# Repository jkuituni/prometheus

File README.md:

# Prometheus

Prometheus is a WDC 65816 based SingleBoardComputer aimed to be a fully usable self-containing computer platform.

System specification:

* CPU: WDC 65816 at 8MHz
* ROM: 8kB Firmware boot EPROM
* RAM: Up to 16MB of RAM via 4x 30pin SIMMs
* Video: Custom graphics chip "GRACE"
* Audio: Ensoniq EN5503 DOC
* I/O: 
  - RS232 serial port
  - Centronics port
  - 2x Atari "standard" joystick ports
  - ps/2 keyboard port
  - IDE massstorage interface
  - Standard floppydrive interface
* Other: 
  - DS1501 Realtime clock
  - 2x 16bit expansion slot connectors
  - 8bit expansion header

The graphics is implemented with a custom video controller called "[GRaCE](https://github.com/jkuituni/GRaCE)" using an additional FPGA board that connects via the two 40pin connectors. 

System controller is a CPLD that ties in the system, It generates the chip selects, various control signals and contains a DRAM controller.

More accurate specifications regarding the memory layout, graphics capabilities and generic system description will be 
added as they become available.

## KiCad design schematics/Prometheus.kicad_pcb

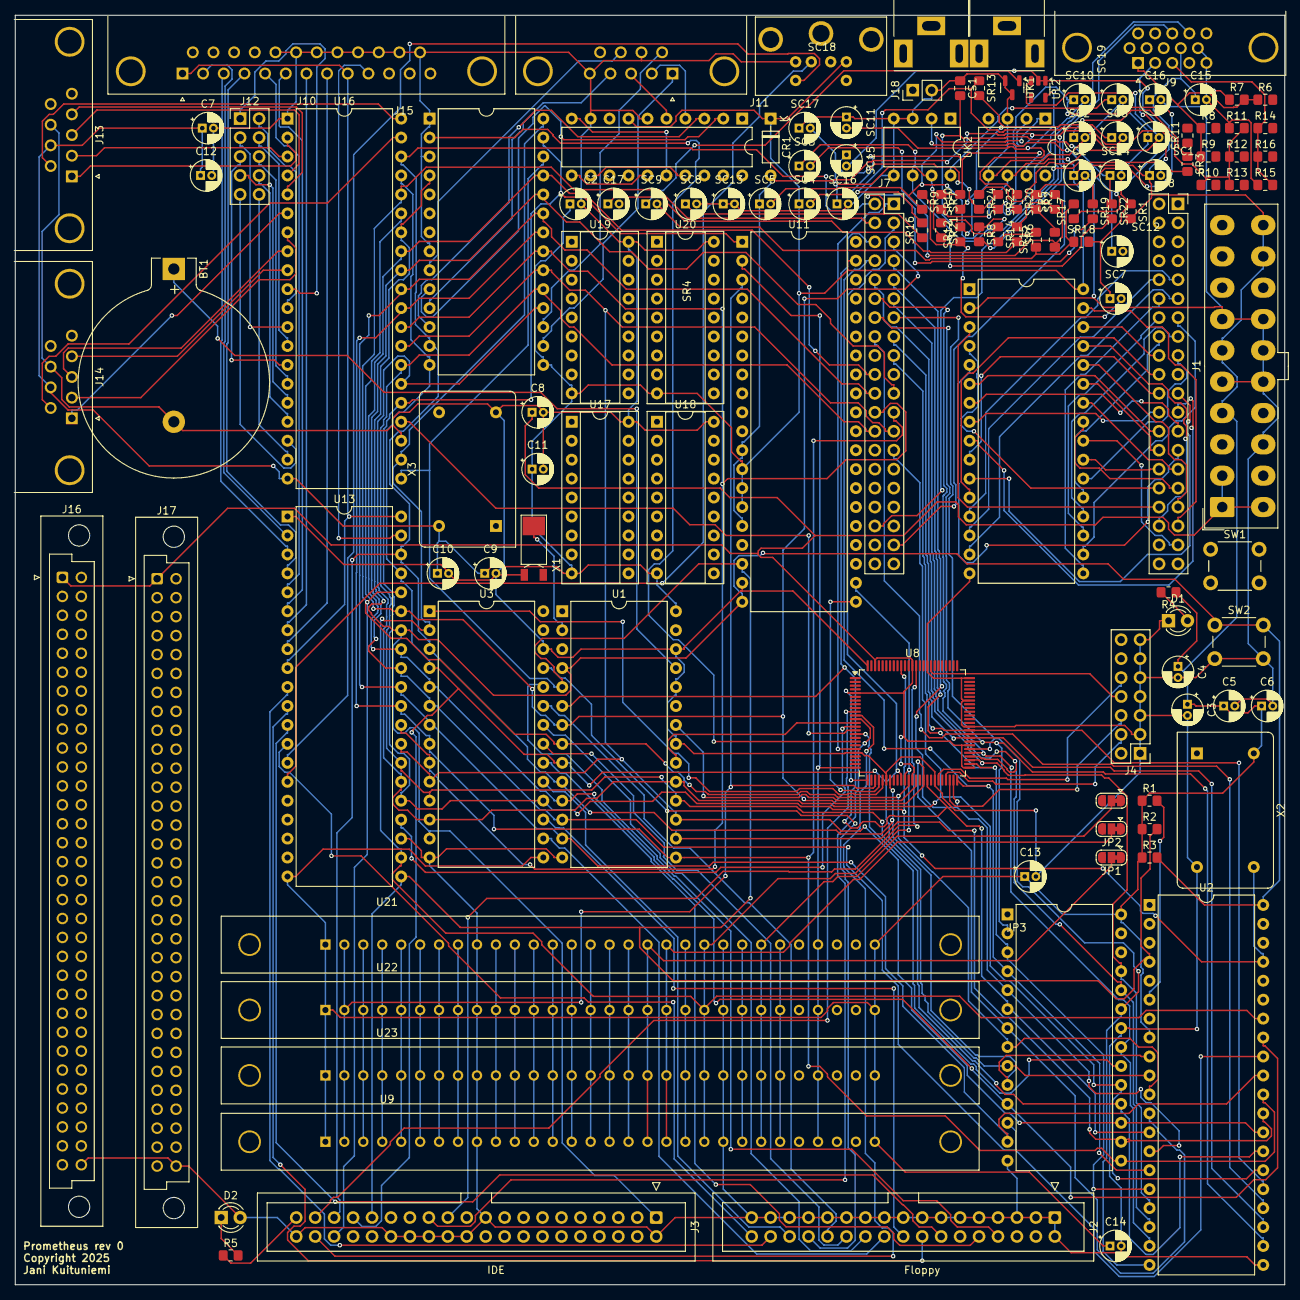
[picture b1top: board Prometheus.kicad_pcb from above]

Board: 2 copper layers, 170.2 x 170.2 mm, 130 parts (0 on the bottom side), 191 nets.

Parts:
BT1: Battery; BatteryHolder_Keystone_104_1x23mm
C1, C2, C3, C4, C5, C6, C7, C8, C9, C10, C11: 0.1uF; CP_Radial_D4.0mm_P1.50mm
C12, C13, C14, C15, C16: C; CP_Radial_D4.0mm_P1.50mm
C17: 0.1u; CP_Radial_D4.0mm_P1.50mm
CR1: 1N914; D_DO-35_SOD27_P7.62mm_Horizontal
CS1: .1u; R_0805_2012Metric_Pad1.20x1.40mm_HandSolder
D1: Power LED; LED_D3.0mm
D2: IDE LED; LED_D3.0mm
J1: ATX Power Conn; Molex_Mini-Fit_Jr_5566-20A_2x10_P4.20mm_Vertical
J2: FDC Connector; IDC-Header_2x17_P2.54mm_Vertical
J3: IDE Connector; IDC-Header_2x20_P2.54mm_Vertical
J4: JTAG; PinHeader_2x07_P2.54mm_Vertical
J5: Left Audio; RCA
J6: Right Audio; RCA
J7: GRACE board interface 1; PinSocket_2x20_P2.54mm_Vertical
J8: GRACE board interface 2; PinSocket_2x20_P2.54mm_Vertical
J9: 15kHz Video Out; DSUB-15-HD_Female_Horizontal_P2.29x1.98mm_EdgePinOffset3.03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
J10: Centronics; DSUB-25_Female_Horizontal_P2.77x2.84mm_EdgePinOffset4.94mm_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
J11: ps/2 keyb; MINI-DIN-6-FULL-SHIELD
J12: Expansion; PinHeader_2x05_P2.54mm_Vertical
J13: Joy1; DSUB-9_Female_Horizontal_P2.77x2.84mm_EdgePinOffset4.94mm_H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
J14: Joy2; DSUB-9_Female_Horizontal_P2.77x2.84mm_EdgePinOffset4.94mm_H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
J15: rs232; DSUB-9_Male_Horizontal_P2.77x2.84mm_EdgePinOffset4.94mm_Hou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
J16, J17: DIN41612_02x32_AB; DIN41612_B_2x32_Female_Vertical_THT
J18: SPEAKER; PinHeader_1x02_P2.54mm_Vertical
JP1, JP2, JP3: Jumper_2_Open; SolderJumper-3_P1.3mm_Bridged12_RoundedPad1.0x1.5mm
R1, R2, R3, R5: R330; R_0805_2012Metric_Pad1.20x1.40mm_HandSolder
R4, R14: R470; R_0805_2012Metric_Pad1.20x1.40mm_HandSolder
R6, R10: R1100; R_0805_2012Metric_Pad1.20x1.40mm_HandSolder
R7, R11, R15: R150; R_0805_2012Metric_Pad1.20x1.40mm_HandSolder
R8, R12: R560; R_0805_2012Metric_Pad1.20x1.40mm_HandSolder
R9, R13: R270; R_0805_2012Metric_Pad1.20x1.40mm_HandSolder
R16: R240; R_0805_2012Metric_Pad1.20x1.40mm_HandSolder
SC1, SC4, SC5, SC6, SC7: 10p; CP_Radial_D4.0mm_P1.50mm
SC2, SC12, SC17: .1u; CP_Radial_D4.0mm_P1.50mm
SC3, SC9, SC16, SC19: 22u; CP_Radial_D4.0mm_P1.50mm
SC8: 1.5n; CP_Radial_D4.0mm_P1.50mm
SC10, SC15: 3.9n; CP_Radial_D4.0mm_P1.50mm
SC11: 220p; CP_Radial_D4.0mm_P1.50mm
SC13: 1.8n; CP_Radial_D4.0mm_P1.50mm
SC14: 470u/16v; CP_Radial_D4.0mm_P1.50mm
SC18: 560p; CP_Radial_D4.0mm_P1.50mm
SR1, SR4: 1K; R_0805_2012Metric_Pad1.20x1.40mm_HandSolder
SR2: 560; R_0805_2012Metric_Pad1.20x1.40mm_HandSolder
SR3: 2.7; R_0805_2012Metric_Pad1.20x1.40mm_HandSolder
SR5: 220; R_0805_2012Metric_Pad1.20x1.40mm_HandSolder
SR6: 100; R_0805_2012Metric_Pad1.20x1.40mm_HandSolder
SR7, SR8, SR9, SR10, SR12, SR13: 3.9K; R_0805_2012Metric_Pad1.20x1.40mm_HandSolder
SR11: 200K; R_0805_2012Metric_Pad1.20x1.40mm_HandSolder
SR14, SR15: 470K; R_0805_2012Metric_Pad1.20x1.40mm_HandSolder
SR16, SR19, SR20: 15K; R_0805_2012Metric_Pad1.20x1.40mm_HandSolder
SR17, SR18, SR23, SR24: 10K; R_0805_2012Metric_Pad1.20x1.40mm_HandSolder
SR21, SR22: 200; R_0805_2012Metric_Pad1.20x1.40mm_HandSolder
SW1: Power Switch; SW_PUSH_6mm
SW2: Reset Switch; SW_PUSH_6mm
U1: DS1501YN; DIP-28_W15.24mm
U2: wdc65c816; DIP-40_W15.24mm
U3: WD1772; DIP-28_W15.24mm
U8: XC9572XL-TQ100; TQFP-100_14x14mm_P0.5mm
U9, U21, U22, U23: SIMM16M; SIMM
U10: 2764; DIP-28_W15.24mm
U11: EN5503DOC; DIP-40_W15.24mm
U12: VRAM; DIP-32_W15.24mm
U13, U16: wdc65c22; DIP-40_W15.24mm
U14: wdc65c51; DIP-28_W15.24mm
U15: MAX233CPP; DIP-20_W7.62mm
U17, U18, U19, U20: 41464; DIP-18_W7.62mm_Socket
UK1: LM3340; SOT-23
UK2: LM380N-8; DIP-8_W7.62mm
UL1: MC34084; DIP-8_W7.62mm
UL2: TL072; SOT-23-5
X1: 32kHz; Crystal_SMD_FrontierElectronics_FM206
X2: 8MHz; Oscillator_DIP-14
X3: 1.8432MHz; Oscillator_DIP-14

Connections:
+12V: SC16.1, SC17.2, SR21.2, SR22.2, UK2.7 (VS)
/Audio/SND-SIG-: CR1.2 (A), SC1.2, SC5.1, SR8.2, U11.12 (VOLFDBK), U11.16 (SIG-), UL1.2 (-)
/Audio/SOUND.H: SR2.2, SR4.2
/RAM & ROM/DQ0: U9.3 (DQ0), U21.3 (DQ0), U22.3 (DQ0), U23.3 (DQ0)
/RAM & ROM/DQ1: U9.6 (DQ1), U21.6 (DQ1), U22.6 (DQ1), U23.6 (DQ1)
/RAM & ROM/DQ2: U9.10 (DQ2), U21.10 (DQ2), U22.10 (DQ2), U23.10 (DQ2)
/RAM & ROM/DQ3: U9.13 (DQ3), U21.13 (DQ3), U22.13 (DQ3), U23.13 (DQ3)
/RAM & ROM/DQ4: U9.16 (DQ4), U21.16 (DQ4), U22.16 (DQ4), U23.16 (DQ4)
/RAM & ROM/DQ5: U9.20 (DQ5), U21.20 (DQ5), U22.20 (DQ5), U23.20 (DQ5)
/RAM & ROM/DQ6: U9.23 (DQ6), U21.23 (DQ6), U22.23 (DQ6), U23.23 (DQ6)
/RAM & ROM/DQ7: U9.25 (DQ7), U21.25 (DQ7), U22.25 (DQ7), U23.25 (DQ7)
A0: J3.35, J7.2, U1.10 (A0), U2.9 (A0), U3.3 (A0), U8.32, U10.10 (A0), U13.38 (RS0), U14.13 (RS0), U16.38 (RS0)
A1: J3.33, J7.3, U1.9 (A1), U2.10 (A1), U3.4 (A1), U8.35, U10.9 (A1), U13.37 (RS1), U14.14 (RS1), U16.37 (RS1)
A2: J3.36, J7.4, U1.8 (A2), U2.11 (A2), U8.37, U10.8 (A2), U13.36 (RS2), U16.36 (RS2)
A3: J7.5, U1.7 (A3), U2.12 (A3), U8.41, U10.7 (A3), U13.35 (RS3), U16.35 (RS3)
A4: J7.6, U1.6 (A4), U2.13 (A4), U8.42, U10.6 (A4)
A5: J7.7, U2.14 (A5), U8.49, U10.5 (A5)
A6: J7.8, U2.15 (A6), U8.50, U10.4 (A6)
A7: J7.9, U2.16 (A7), U8.52, U10.3 (A7)
A8: J7.10, U2.17 (A8), U8.53, U10.25 (A8)
A9: J7.11, U2.18 (A9), U8.54, U10.24 (A9)
A10: J7.12, U2.19 (A10), U8.55, U10.21 (A10)
A11: J7.13, U2.20 (A11), U8.56, U10.23 (A11)
A12: J7.14, U2.22 (A12), U8.58, U10.2 (A12)
A13: J7.15, U2.23 (A13), U8.59
A14: J7.16, U2.24 (A14), U8.60
A15: J7.17, U2.25 (A15), U8.61
AUDIO_EN: U8.29, U11.21 (~CS)
CAS: U8.28, U9.2 (CAS), U11.3 (~CAS), U21.2 (CAS), U22.2 (CAS), U23.2 (CAS)
D0: J7.20, U1.11 (DQ0), U2.33 (D0), U3.5 (DAL0), U10.11 (D0), U13.33 (D0), U14.25 (D7), U16.33 (D0)
D1: J7.21, U1.12 (DQ1), U2.32 (D1), U3.6 (DAL1), U10.12 (D1), U13.32 (D1), U14.24 (D6), U16.32 (D1)
D2: J7.22, U1.13 (DQ2), U2.31 (D2), U3.7 (DAL2), U10.13 (D2), U13.31 (D2), U14.23 (D5), U16.31 (D2)
D3: J7.23, U1.15 (DQ3), U2.30 (D3), U3.8 (DAL3), U10.15 (D3), U13.30 (D3), U14.22 (D4), U16.30 (D3)
D4: J7.24, U1.16 (DQ4), U2.29 (D4), U3.9 (DAL4), U10.16 (D4), U13.29 (D4), U14.21 (D3), U16.29 (D4)
D5: J7.25, U1.17 (DQ5), U2.28 (D5), U3.10 (DAL7), U10.17 (D5), U13.28 (D5), U14.20 (D2), U16.28 (D5)
D6: J7.26, U1.18 (DQ6), U2.27 (D6), U3.11 (DAL6), U10.18 (D6), U13.27 (D6), U14.19 (D1), U16.27 (D6)
D7: J7.27, U1.19 (DQ7), U2.26 (D7), U3.12 (DAL7), U10.19 (D7), U13.26 (D7), U14.18 (D0), U16.26 (D7)
FDC_DRVA: J2.14, U13.12 (PB2)
FDC_DSKCHG: J2.34, U13.13 (PB3)
FDC_EN: U3.1 (~CS), U8.30
FDC_MTREN: J2.16, U13.11 (PB1)
FDC_SIDE: J2.32, U13.10 (PB0)
GND: BT1.2 (-), C1.2, C2.2, C3.2, C4.2, C5.2, C6.2, C7.2, C8.2, C9.2, C10.2, C11.2, C12.2, C13.2, C14.2, C15.2, C16.2, D1.1 (K), D2.2 (A), J1.5, J1.7, J1.13, J1.15, J1.16, J1.17, J2.1, J2.2, J2.3, J2.5, J2.7, J2.9, J2.11, J2.13, J2.15, J2.17, J2.19, J2.21, J2.23, J2.25, J2.27, J2.29, J2.31, J2.33, J3.2, J3.19, J3.22, J3.24, J3.26, J3.28, J3.30, J3.40, J4.1, J4.3, J4.5, J4.7, J4.9, J4.11, J4.13, J9.5, J9.10, J10.18, J10.19, J10.20, J10.21, J10.22, J10.23, J10.24, J10.25, J11.3, J13.8, J14.8, J15.5, J15.7, J16.b32, J17.b32, R7.1, R11.1, R15.1, SR2.1, SW2.2 (B), U1.14 (GND), U1.21 (GND), U1.24 (~KS), U1.26 (Vbaux), U2.21 (VSS), U3.14 (GND), U3.26 (~DDEN), U8.21 (GND), U8.31 (GND), U8.44 (GND), U8.62 (GND), U8.69 (GND), U8.75 (GND), U8.84 (GND), U8.100 (GND), U9.9 (GND), U9.22 (GND), U10.14 (GND), U10.22 (~OE), U11.19 (VSS), U12.2 (A16), U12.16 (GND), U13.1 (Vss), U13.23 (~CS2), U14.1 (VSS), U14.3 (~CS1), U14.8 (~RTS), U15.6 (GND), U15.9 (GND), U16.1 (Vss), U16.23 (~CS2), U17.18 (GND), U18.18 (GND), U19.18 (GND), U20.18 (GND), U21.9 (GND), U21.22 (GND), U22.9 (GND), U22.22 (GND), U23.9 (GND), U23.22 (GND), X1.2 (GND), X2.7 (GND), X3.7 (GND)
GNDA: CS1.1, J18.2, SC2.2, SC7.1, SC8.2, SC11.1, SC13.1, SC13.2, SC14.2, SC16.2, SC17.1, SC18.1, SC19.2, SR1.1, SR12.2, SR18.2, UK1.2, UK1.3, UK2.3 (-), UK2.4 (GND), UK2.5 (GND), UL1.3 (+), UL1.5 (+)
GNDPWR: C17.1, SR6.2
GRACE_EN: J7.1, U8.20
IDE_CS0: J3.37, U8.10
IDE_CS1: J3.38, U8.11
IOR: J3.25, U8.12
IOW: J3.23, U8.87
IRQ: J3.31, R2.2, U1.5 (~IRQ), U2.4 (~IRQ), U11.18 (~IRQ), U13.21 (~IRQ), U14.26 (~IRQ), U16.21 (~IRQ)
MA0: U9.4 (A0), U21.4 (A0), U22.4 (A0), U23.4 (A0)
MA1: U9.5 (A1), U21.5 (A1), U22.5 (A1), U23.5 (A1)
MA2: U9.7 (A2), U21.7 (A2), U22.7 (A2), U23.7 (A2)
MA3: U9.8 (A3), U21.8 (A3), U22.8 (A3), U23.8 (A3)
MA4: U9.11 (A4), U21.11 (A4), U22.11 (A4), U23.11 (A4)
MA5: U9.12 (A5), U21.12 (A5), U22.12 (A5), U23.12 (A5)
MA6: U9.14 (A6), U21.14 (A6), U22.14 (A6), U23.14 (A6)
MA7: U9.15 (A7), U21.15 (A7), U22.15 (A7), U23.15 (A7)
MA8: U9.17 (A8), U21.17 (A8), U22.17 (A8), U23.17 (A8)
MA9: JP1.1 (A), JP1.2 (B), U9.18 (A9), U21.18 (A9), U22.18 (A9), U23.18 (A9)
MA10: JP2.1 (A), JP2.2 (B), U9.19 (A10), U21.19 (A10), U22.19 (A10), U23.19 (A10)
MA11: JP3.1 (A), JP3.2 (B), U9.24 (A11), U21.24 (A11), U22.24 (A11), U23.24 (A11)
NMI: R1.2, U2.6 (~NMI)
unnamed: BT1.1 (+), U1.25 (Vbat)
unnamed: D1.2 (A), R4.2
unnamed: D2.1 (K), R5.2
unnamed: J2.8, U3.24 (~IP)
unnamed: J2.10, U3.20 (MO)
unnamed: J2.18, U3.17 (DIRC)
unnamed: J2.20, U3.16 (STEP)
unnamed: J2.22, U3.22 (WD)
unnamed: J2.24, U3.21 (WG)
unnamed: J2.26, U3.23 (~TR00)
unnamed: J2.28, U3.25 (~WPRT)
unnamed: J2.30, U3.19 (~RD)
unnamed: J3.39, R5.1
unnamed: J4.4, U8.47 (TMS)
unnamed: J4.6, U8.48 (TCK)
unnamed: J4.8, U8.83 (TDO)
unnamed: J4.10, U8.45 (TDI)
unnamed: J7.36, J9.14
unnamed: J7.37, J9.13
unnamed: J8.9, U12.13 (Q0)
unnamed: J8.10, U12.14 (Q1)
unnamed: J8.11, U12.15 (Q2)
unnamed: J8.12, U12.17 (Q3)
unnamed: J8.13, U12.18 (Q4)
unnamed: J8.14, U12.19 (Q5)
unnamed: J8.15, U12.20 (Q6)
unnamed: J8.16, U12.21 (Q7)
unnamed: J8.17, U12.22 (~CS1)
unnamed: J8.18, U12.30 (CS2)
unnamed: J8.20, U12.12 (A0)
unnamed: J8.21, U12.11 (A1)
unnamed: J8.22, U12.10 (A2)
unnamed: J8.23, U12.9 (A3)
unnamed: J8.24, U12.8 (A4)
unnamed: J8.25, U12.7 (A5)
unnamed: J8.26, U12.6 (A6)
unnamed: J8.27, U12.5 (A7)
unnamed: J8.28, U12.27 (A8)
unnamed: J8.29, U12.26 (A9)
unnamed: J8.30, U12.23 (A10)
unnamed: J8.31, U12.25 (A11)
unnamed: J8.32, U12.4 (A12)
unnamed: J8.33, U12.28 (A13)
unnamed: J8.34, U12.3 (A14)
unnamed: J8.35, U12.31 (A15)
unnamed: J8.36, U12.29 (~WE)
unnamed: J8.37, U12.24 (~OE)
unnamed: J9.1, R6.1, R7.2, R8.1, R9.1
unnamed: J9.2, R10.1, R11.2, R12.1, R13.1
unnamed: J9.3, R14.1, R15.2, R16.1
unnamed: J12.1, U16.10 (PB0)
unnamed: J12.2, U16.11 (PB1)
unnamed: J12.3, U16.12 (PB2)
unnamed: J12.4, U16.13 (PB3)
unnamed: J12.5, U16.14 (PB4)
unnamed: J12.6, U16.15 (PB5)
unnamed: J12.7, U16.16 (PB6)
unnamed: J12.8, U16.17 (PB7)
unnamed: J12.9, U16.18 (CB1)
unnamed: J12.10, U16.19 (CB2)
unnamed: SC3.2, SR4.1, SR5.2
unnamed: SR5.1, SR6.1
unnamed: SR14.2, SR15.2
unnamed: SC2.1, SR3.1
unnamed: SC3.1, SR3.2, UK2.6
unnamed: SC4.2, SR7.1, SR10.2, UL1.7
unnamed: SC5.2, SR8.1, SR9.2, UL1.1
unnamed: SC6.2, SR13.1, SR16.2
unnamed: SC8.1, SR16.1, SR19.2
unnamed: SC9.1, UK1.1
unnamed: SC9.2, SR15.1, SR17.2, SR18.1
unnamed: SC10.1, SR19.1, SR20.2
unnamed: SC15.1, SR23.1, SR24.2
unnamed: CS1.2, SC14.1, SR14.1, SR21.1, SR22.1
unnamed: J10.1, J10.9, U13.9 (PA7), U13.40 (CA1)
unnamed: J10.10, U13.39 (CA2)
unnamed: J10.2, U13.2 (PA0)
unnamed: J10.3, U13.3 (PA1)
unnamed: J10.4, U13.4 (PA2)
unnamed: J10.5, U13.5 (PA3)
unnamed: J10.6, U13.6 (PA4)
unnamed: J10.7, U13.7 (PA5)
unnamed: J10.8, U13.8 (PA6)
unnamed: J11.5, U13.14 (PB4)
unnamed: J11.1, U13.15 (PB5)
unnamed: U14.12 (RxD), U15.3 (R1OUT)
unnamed: U14.10 (TxD), U15.2 (T1IN)
unnamed: J15.8, U14.9 (~CTS)
unnamed: J15.1, U14.16 (~DCD)
unnamed: J15.6, U14.17 (~DSR)
unnamed: J15.4, U14.11 (~DTR)
unnamed: U15.11 (C2+(C2-)), U15.15 (C2+)
unnamed: U15.10 (V-(CS-)), U15.16 (C2-)
unnamed: J15.2, U15.4 (R1IN)
unnamed: J15.3, U15.5 (T1OUT)
unnamed: U15.12 (V-(C2+)), U15.17 (V-)
unnamed: J13.6, U16.40 (CA1)
unnamed: J14.6, U16.39 (CA2)
unnamed: J13.1, U16.2 (PA0)
unnamed: J13.2, U16.3 (PA1)
unnamed: J13.3, U16.4 (PA2)
unnamed: J13.4, U16.5 (PA3)
unnamed: J14.1, U16.6 (PA4)
unnamed: J14.2, U16.7 (PA5)
unnamed: J14.3, U16.8 (PA6)
unnamed: J14.4, U16.9 (PA7)
unnamed: SC12.1, UK2.2 (+)
unnamed: SC19.1, UK2.8 (BYPASS)
unnamed: SC7.2, SR9.1, SR12.1
unnamed: SC6.1, SR10.1, SR13.2
unnamed: SC18.2, SR24.1, UL2.3 (+)
unnamed: SC15.2, SR17.1, UL2.1, UL2.2 (-)
unnamed: SC11.2, SR20.1, UL2.5 (+)
unnamed: SC10.2, SR23.2
PHI2: U2.37 (PHI2), U3.18 (CLK), U8.91, U11.1 (CLK), U13.25 (PHI2), U14.27 (PHI2), U16.25 (PHI2), X2.8 (OUT)
RAS: U8.25, U9.27 (RAS), U11.2 (~RAS), U21.27 (RAS), U22.27 (RAS), U23.27 (RAS)
RES: J3.1, R3.2, SW2.1 (A), U1.4 (~RST), U2.40 (~RES), U3.13 (~MR), U11.20 (RES), U13.34 (~RES), U14.4 (~RES), U16.34 (~RES)
ROM_EN: U8.16, U10.20 (~CE)
RTC_CLK: U1.2 (X1), X1.3 (OUT)
RTC_EN: U1.20 (~CE), U8.13
RW: U2.34 (~RW), U3.2 (~RW), U8.36, U9.21 (WR), U11.22 (~WE), U13.22 (~RW), U14.28 (~RW), U16.22 (~RW), U21.21 (WR), U22.21 (WR), U23.21 (WR)
UART_EN: U8.18, U14.2 (CS0)
VIA1_EN: U8.14, U13.24 (CS1)
VIA2_EN: U8.15, U16.24 (CS1)
Vcc: C1.1, C2.1, C3.1, C4.1, C5.1, C6.1, C7.1, C9.1, C10.1, C11.1, C12.1, C13.1, C14.1, C15.1, C16.1, CR1.1 (K), J1.4, J1.6, J1.19, J1.20, J9.9, J11.4, J13.7, J14.7, R1.1, R2.1, R3.1, R4.1, SC1.1, SC4.1, SR1.2, SR7.2, U1.28 (Vcc), U2.8 (VDD), U3.15 (VCC), U9.1 (VCC), U9.30 (VCC), U10.28 (VCC), U11.13 (VOL-), U11.14 (WVREF), U11.15 (SIG+), U11.39 (VDD), U12.32 (VCC), U13.20 (VDD), U14.15 (VDD), U15.7 (VCC), U16.20 (VDD), U17.9 (VCC), U18.9 (VCC), U19.9 (VCC), U20.9 (VCC), U21.1 (VCC), U21.30 (VCC), U22.1 (VCC), U22.30 (VCC), U23.1 (VCC), U23.30 (VCC), UL1.6 (-), X2.14 (Vcc), X3.14 (Vcc)
Vcc33: C8.1, J1.1, J1.2, J1.11, J16.a1, J17.a1, U8.5 (VCC), U8.26 (VCCIO), U8.38 (VCCIO), U8.51 (VCCIO), U8.57 (VCC), U8.88 (VCCIO), U8.98 (VCC)
~OE: U1.22 (~OE), U8.39

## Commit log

2020-06-27 Initial commit for Prometheus single board computer.
2020-06-27 Updates to README
2020-06-28 add .gitignore
2020-06-28 clean up temporary files from repository
2020-06-28 Remove old projects and associated stuff
2020-06-28 Remove obsolete rescue library
2020-06-28 Move No Connect on ATX pin 12 to actual pin
2020-06-28 Remove unneeded libaries from schematic library
2020-06-29 Cleanup and spot check for main sheet
2020-06-29 add box around DS1501
2020-06-29 Added 8bit to 16bit IDE data handling latching.
2020-06-29 draw boxes and fix power pins
2020-06-29 replace components in sheets
2020-06-30 Fixup heirarchial labels
2020-06-30 add audio schematic, other fixes
2020-06-30 Removed EN5503DOC chip from IO2 sheet as it is now on it's own separate sheet. Changed description texts to reflect the change.
2020-06-30 Adjusted the README
2020-06-30 Minor adjustment to io-2 sheet.
2020-07-02 Re-added 8->16bit IDE data handling via latches and buffers.
2020-07-09 Added missing IDE control signals for the latches, bus drivers, reads/writes and chip selects.
2020-07-09 Added missing FDC control signals.
2020-07-09 Fixes to FDC signal mapping.
2020-07-09 Fixes to chip references.
2020-07-09 Minor tweaks to labels and values.
2020-07-09 Added support for Diskchange for FDC interface.
2020-07-09 Added 74ls245 and 74ls574 chip datasheets.
2020-07-11 Add missing RAM MA-bus symbol.
2020-07-14 Replace global labels with herarchial labels
2020-07-14 separate HDD from FDD, prepare to connect pins
2020-07-17 rework to include net labels, high IRQ line for FDC
2020-07-17 cosmetic work
2020-07-17 connect up I/O sheet 2
2020-07-17 Use the right component, idiot...
2020-07-17 Opposite PHI2 and RWB trigger bank address on d0..7
2020-07-17 Just so I don't forget...
2020-07-18 another note for the future
2020-07-18 add bus labels, hierarchial labels
2020-07-18 rename A[0..23] to A[0..15]
2020-07-18 begin wiring up the hierarchial sheets
2020-07-19 Issue #4: Remove RAM_EN pin
2020-07-19 Add SIMM size select jumpers
2020-07-19 rearrange schematic page
2020-07-19 clean up, added nc pins
2020-07-19 Finish connecting hierarchial pins
2020-07-19 finish up hierarchial pins (as they stand now)
2020-07-20 additional fixups
2020-07-28 Added a few lost power connections and no_connect entries.
2025-01-19 Added a whole bunch of footprints for symbols.
2025-01-19 Initial PCB layout and autoroute. Still lots missing.
2025-02-04 Small tweaks here and there. Added a lot of missing footprint definitions.
2025-02-04 Initial PCB layout and route.
2025-02-04 Added some missing footprints.
2025-02-04 Added analog audio section. Followed Apple IIGS schematics for this one as it uses the same EN5503DOC audio chip. Still a bit unclear how to connect the RCA jacks instead of the phonejack and analog 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
2025-02-05 Added a lot of missing footprints in the audio-section. Adjusted the PCB layout and re-routed the board.
2025-02-06 Added the rest of the footprints for the analog audio and re-did the layout and routing of the PCB.
2025-02-07 Add more datasheets for parts used in the audio-section.
2026-01-23 Updated README.
2026-01-28 First draft of system CPLD controller logic. Includes address decoder and DRAM controller for the SIMM modules.
2026-02-03 Minor RAM memory spec adjustment.

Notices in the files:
schematics/Prometheus.kicad_pcb:
Copyright 2025
